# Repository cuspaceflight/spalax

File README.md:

# Spalax

This repository contains the schematics, PCB designs and firmware for a 10DOF IMU system.

## Components

- [Firmware](firmware) - Firmware for the various IMU boards
- [GUI](gui) - A 3D visualisation GUI which renders in realtime data sent from an attached IMU board
- [Shared](shared) - A static library providing common functionality between the various software components
- [Util](util) - A collection of useful C++, python and bash utilities
- [PCB](pcb) - The KiCad PCB files for the Spalax IMU boards

## Build Requirements

- GCC v4.8+
- CMake v3.2+
- arm-none-eabi-gcc (firmware build)
- xorg-dev libgl1-mesa-dev libfreetype6-dev libglew-dev libglm-dev (GUI build)
- GLFW v3+ (GUI build) - see [glfw-install.sh](util/bash/glfw-install.sh)

## Compilation

Having installed all the dependencies simply run from the root directory of the repo

```bash
git submodule update --init --recursive
./util/bash/travis-build.sh
```

This will configure and compile all the different components. If you only wish to configure a subset, just run the relevant section of [travis-build.sh](util/bash/travis-build.sh).

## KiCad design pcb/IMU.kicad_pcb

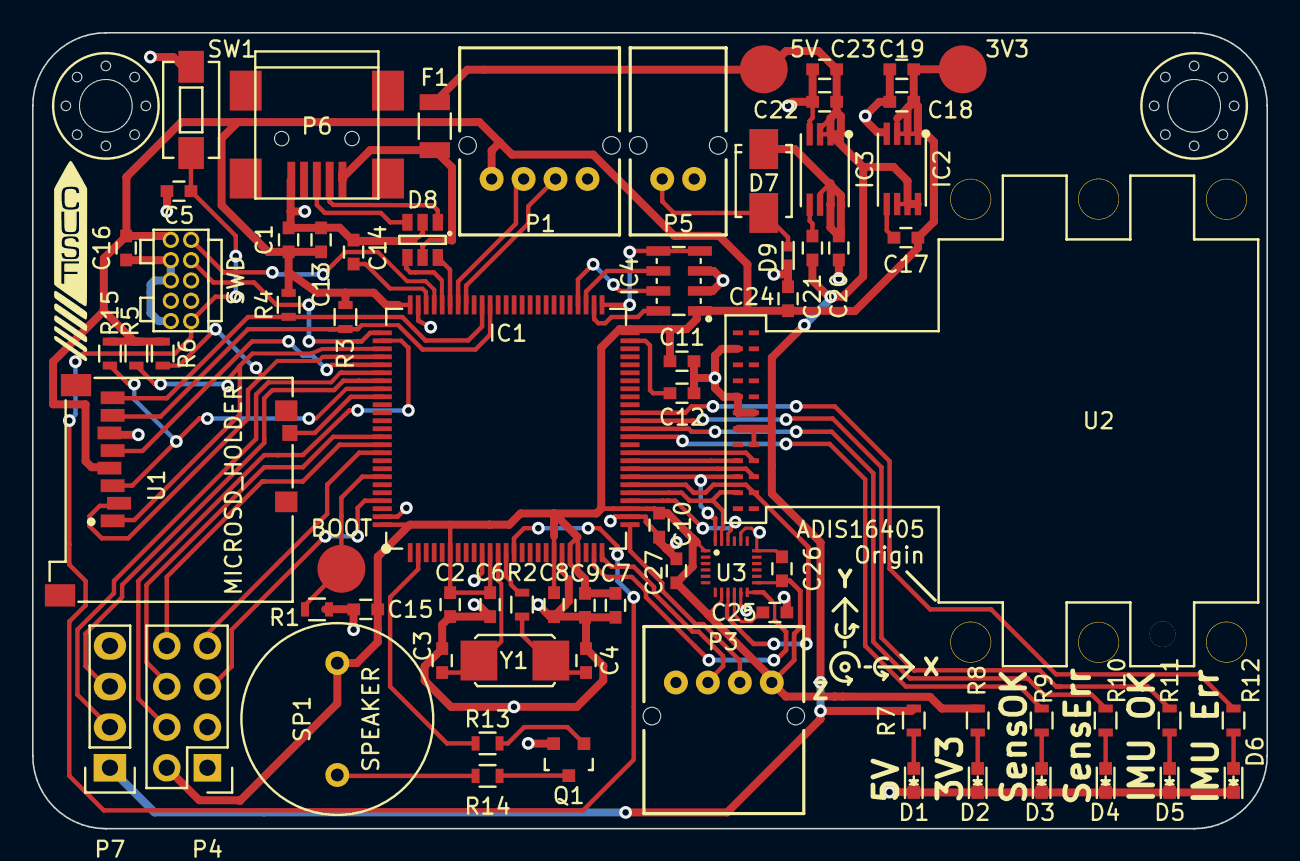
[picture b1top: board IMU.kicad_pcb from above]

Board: 2 copper layers, 77.2 x 49.8 mm, 75 parts (0 on the bottom side), 66 nets.

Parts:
3V3: 3V3; Measurement_Point_Round-SMD-Pad_Big
5V: 5V; Measurement_Point_Round-SMD-Pad_Big
BOOT: BOOT0; Measurement_Point_Round-SMD-Pad_Big
C1, C19, C23: 10µ; C_0603
C2, C5, C6, C8, C10, C11, C13, C15, C16, C24, C25, C27: 100n; C_0603
C3, C4: 15p; C_0603
C7, C18, C20, C22: 1µ; C_0603
C9, C26: 10n; C_0603
C12, C14: 2µ2; C_0603
C17, C21: 1n; C_0603
D1, D2, D3, D5: LED_GREEN; LED-0603
D4, D6: LED_RED; LED-0603
D7: S1A; SMA_Standard
D8: USBLC6-2; SOT-23-6
D9: CGA0402MLC-12G; R0402
F1: 500mA; MC33191
IC1: STM32F405VGT; LQFP100
IC2: ADP3335ARMZ-3.3; MSOP8
IC3: ADP3335ARMZ-5; MSOP8
IC4: MS5611-01BA03; MS5611-01BA
M3_MOUNT, M3_MOUNT#2: VAL**; M3_MOUNT
P1: UART1; S04B-PASK-2
P2: SWD; FTSH-105-01-F-D-K
P3: UART2; S04B-PASK-2
P4: SPI; Pin_Header_Straight_2x04
P5: BATTERY; S02B-PASK-2
P6: USB_OTG; USB_Mini-B
P7: CAN BUS; Pin_Header_Straight_1x04
Q1: Q_NMOS_GSD_PSV; SOT-23
R1: 10K; R_0603
R2, R13: 100; R_0603
R3, R4, R5, R6, R15: 47k; R_0603
R7: 1k; R_0603
R8, R9, R10, R11, R12: 510; R_0603
R14: 10; R_0603
SP1: SPEAKER; ABI-042-RC
SW1: SW_PUSH; SW_SPST_EVQPE1
U1: MICROSD_HOLDER; MEM2051
U2: ADIS16405BMLZ
U3: MOTION/POSITION-MPU-9250(QFN24); QFN24G-0.4-3X3MM
Y1: 8M; XTAL50x32

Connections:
+3V3: 3V3.1, C1.1, C2.1, C6.1, C7.1, C8.1, C9.1, C10.1, C11.1, C13.1, C15.1, C16.1, C17.1, C18.1, C19.1, C24.1, C26.2, C27.1, IC1.6, IC1.11, IC1.19, IC1.21, IC1.22, IC1.28, IC1.50, IC1.75, IC1.100, IC2.1, IC2.2, IC2.3, IC4.1, P1.1, P2.1, P3.1, P4.2, R3.1, R4.1, R5.1, R6.1, R8.2, R15.1, SP1.1, U1.4, U3.1, U3.8, U3.13
+5V: 5V.1, C21.1, C22.1, C23.1, F1.2, IC2.6, IC2.7, IC2.8, IC3.1, IC3.2, IC3.3, P7.1, R7.2, U2.10, U2.11, U2.12
+BATT: C20.1, D7.1, IC3.6, IC3.7, IC3.8
/Altimeter/ALT_CSB: IC1.51, IC4.4, IC4.5
/Altimeter/ALT_SCLK: IC1.52, IC4.8
/Altimeter/ALT_SDI: IC1.54, IC4.7
/Altimeter/ALT_SDO: IC1.53, IC4.6
/BOOT0: BOOT.1, IC1.94, R1.2
/CAN1_RX: IC1.81, P7.2
/CAN1_TX: IC1.82, P7.3
/DATA_RDY: IC1.97, P4.5
/IntertialSensors/ADIS_IRQ: IC1.34, U2.7
/IntertialSensors/MISO: IC1.31, U2.4, U3.9
/IntertialSensors/MOSI: IC1.32, U2.5, U3.24
/IntertialSensors/MPU_IRQ: IC1.24, U3.12
/IntertialSensors/SCLK: IC1.30, U2.3, U3.23
/IntertialSensors/~ADIS_RESET: IC1.35, U2.8
/IntertialSensors/~ADIS_SS: IC1.33, U2.6
/IntertialSensors/~MPU_SS: IC1.29, U3.22
/Power/USB5V: D8.5, F1.1, P6.1
/SDCard/CARD_DETECT: IC1.84, U1.9
/SDCard/SDIO_CK: IC1.80, U1.5
/SDCard/SDIO_CMD: IC1.83, R15.2, U1.3
/SDCard/SDIO_D0: IC1.65, R3.2, U1.7
/SDCard/SDIO_D1: IC1.66, R4.2, U1.8
/SDCard/SDIO_D2: IC1.78, R5.2, U1.1
/SDCard/SDIO_D3: IC1.79, R6.2, U1.2
/SPI3_MISO: IC1.90, P4.8
/SPI3_MOSI: IC1.91, P4.7
/SPI3_NSS: IC1.77, P4.4
/SPI3_SCK: IC1.89, P4.6
/SWDCLK: IC1.76, P2.4
/SWDIO: IC1.72, P2.2
/StatusIndicators/Buzzer: IC1.2, R13.2
/StatusIndicators/IMU: IC1.39, R11.2
/StatusIndicators/Sensors: IC1.37, R9.2
/StatusIndicators/~IMU: IC1.40, R12.2
/StatusIndicators/~Sensors: IC1.38, R10.2
/USART1_RX: IC1.69, P1.2
/USART1_TX: IC1.68, P1.3
/USART2_RX: IC1.26, P3.2
/USART2_TX: IC1.25, P3.3
/USB/OTG_DS_DP: D8.4, IC1.71
/USB/OTG_FS_DM: D8.6, IC1.70
/~RST: C5.1, IC1.14, P2.10, SW1.2
GND: C1.2, C2.2, C3.2, C4.2, C5.2, C6.2, C7.2, C8.2, C9.2, C10.2, C11.2, C12.2, C13.2, C14.2, C15.2, C16.2, C18.2, C19.2, C20.2, C22.2, C23.2, C24.2, C25.1, C26.1, C27.2, D1.1, D2.1, D3.1, D4.1, D5.1, D6.1, D8.2, D9.1, IC1.10, IC1.20, IC1.27, IC1.74, IC1.99, IC2.4, IC3.4, IC4.2, IC4.3, P1.4, P2.3, P2.5, P2.9, P3.4, P4.1, P4.3, P5.2, P6.5, P7.4, Q1.2, R1.1, SW1.1, U1.6, U2.13, U2.14, U2.15, U2.21, U3.11, U3.18, U3.20
unnamed: C3.1, IC1.12, Y1.1
unnamed: C4.1, R2.2, Y1.2
unnamed: C12.1, IC1.49
unnamed: C14.1, IC1.73
unnamed: C17.2, IC2.5
unnamed: C21.2, IC3.5
unnamed: C25.2, U3.10
unnamed: D1.2, R7.1
unnamed: D2.2, R8.1
unnamed: D3.2, R9.1
unnamed: D4.2, R10.1
unnamed: D5.2, R11.1
unnamed: D6.2, R12.1
unnamed: D7.2, D9.2, P5.1
unnamed: D8.1, P6.2
unnamed: D8.3, P6.3
unnamed: IC1.13, R2.1
unnamed: Q1.1, R13.1
unnamed: Q1.3, R14.1
unnamed: R14.2, SP1.2

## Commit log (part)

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2015-10-30 add ADIS16405BMLZ symbol and footprint
    Analog Devices kindly provide downloadable footprints and schematic symbols for
    the sensor. Unfortunately they're in a format which requires running a quite god
    awful tool to convert them into something usable. After firing up the Windows 10
    VM image I've got lying around, I finally got the damn things in KiCad format.
    Add them to the repo to save some other poor fool the effort.
    [1] http://www.analog.com/en/design-center/packaging-quality-symbols-footprints/symbols-and-footprints.html
2015-10-30 PCB/.gitignore: ignore KiCad backup files
2015-11-01 README: add link to some resources
2015-11-03 Added ADIS16405BMLZ schematic to InertialSensors sheet.
2015-11-03 Added Altimeter work by Alex Clowes
2015-11-04 remove special library
2015-11-04 PCB/IMU.sh: replace Earth symbols with Ground symbols
    Best be consistent!
2015-11-05 PCB/IMU.sch: add global labels for each pin assignment
2015-11-05 PCB: wire up altimeter to SPI2
2015-11-11 Basic firmware setup
2015-11-12 ekf-notes: fix type mathbf -> mathbb
2015-11-12 ekf-notes: move paragraph on setting predicted state components
    The paragraph on imposing certain predicted state components was in a
    non-logical place.
2015-11-12 ekf-notes: add some words on extending to linear motion
2015-11-12 ekf-notes: fix subscript of quaternion parameterisation
2015-11-12 README: add link to Madgwick's paper
2015-11-13 Revert to commit before last to fix bugs introduced by last commit
2015-11-15 wire IMU sensors to SPI1
2015-11-15 PCB: add test point to allow manual toggling of BOOT0
2015-11-15 PCB: annotate schematic and remove unused SDIO pins
2015-11-15 PCB: update TODO (remove done items)
2015-11-16 PCB: place components around STM32
    Those components whose placing is required to be close to particular pads have
    been placed and routed.
2015-11-16 PCB: swap some GPIO pin assignment to improve layout
    We have considerable freedom wrt GPIO pin locations. Route the inertial sensor's
    data ready line to a useful side of the chip.
2015-11-16 PCB: re-draw the ADIS16405 symbol to be less ugly
2015-11-16 PCB: fix footprint name of ADIS16450
2015-11-16 add ESD protection
2015-11-17 Updated README.md with information on how to configure Firmware and GUI builds.
2015-11-17 Further gitignore fixes.
2015-11-17 add simple Travis CI configuration
    Add .travis.yml and associated .editoconfig to support a minimal build of the
    firmware on Travis CI.
    The configuration selects Trusty as the build machine since it is the earliest
    version of Ubuntu LTS which includes the ARM GCC toolchain. (And the only one
    available on Travis.)
2015-11-18 PCB: SDCard: check Farnell numbers & footprints
2015-11-18 PCB: USB: check Farnell numbers & footprints
2015-11-18 PCB: re-import netlist with new footprints
2015-11-18 PCB: add xml2farnell.py script
    (Complete with unicode fixes)
2015-11-18 Add 2x4 pin header footprint for SPI connector
2015-11-18 PCB: add first pass at Farnell BOM
2015-11-29 Initial work on kalman filter - currently incomplete and in need of major cleanup
2015-11-30 Fixed Firmware build.
2015-12-02 update ADIS16405BMLZ footprint to have bigger pads
2015-12-04 Edit design rules so mimimums are (at least) m2fc values
2015-12-05 Move components to likely final locations and adjust some trace widths
2015-12-13 Move status LED outputs to pins 33 to 36 of the microcontroller
2015-12-14 Fixed bug where the indices of the jacobians were swapped, resulting in rather strange behaviour.
    The filter now works very well, the only problem remaining is roll isn't always resolved correctly. I'm not sure this is a deficiency of the filter, however, as the magnetometer on the board I am usi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
2015-12-19 Reduced number of long traces in ground plane by shuffling a number of components around. Also reduced the length of the PCB as an added bonus.
    The silkscreen is currently messed up as a result of these changes - I've not had time to fix it.
2016-01-11 Added an MPU-9250 on the same SPI bus as the ADIS sensor. The PCB routing is a first draft and I may tweak it a bit further.
    I had to change the track spacing tolerance from 0.2mm to 0.19mm to be able to wire up the sensor.
2016-01-20 Added badthinghandler written by James Timmins
2016-01-22 Added outline for mpu9250 driver
    Added ID check to ADIS16405 driver
    Minor tweaks to badthinghandler
2016-01-28 Changed SD Card resistors to 47K and changed ADIS reset to be attached to a GPIO pin instead.
2016-01-28 Add IMU axes and origin to PCB
2016-01-28 Imported new netlist into PCBNew and placed new footprints.
2016-01-28 Further PCB routing.
2016-01-29 Updated MPU9250 schematic part to match MPU-9250
    Fixed directionality of hierarchical pins
2016-01-31 Remove old Gerbers, add zip of gerbers sent to manufacturing.
2016-02-08 Pin and board configuration
2016-02-09 update pcb for paste generation
2016-03-12 MPU fixes
2016-03-12 firmware:mpu9520: explicitly ignore argument to thread
    ChibiOS threads may take an argument used to initialise them. The MPU9250 threa
    does not but we should explicitly indicate this both to the compiler *and* to
    humans.
2016-03-13 firmware:mpu9250: add gyro self-test to init sequence
    Re-jig mpu9250_init() to use a table of registers and values to make it a little
    easier to edit. Also call (and check return value of) mpu9250_self_test_gyro()
    to perform a self-test on the gyroscope.
    It's non-obvious where to find the application note referenced in the datasheet
    on self-testing. Instead I've cribbed from other MPU9250 drivers and implemented
    the same self-test algorithm.
2016-03-13 firmware:mpu9250: implement accelerometer self-test as well
2016-03-14 firmware:mpu9250: re-factor self-test
    The previous implementation ran the gyroscope self test at the same time as the
    accelerometer self test. This is a Bad Idea since they may interfere with each
    other. Re-factor the code to do them sequentially. Also remove the needlessly
    complex mean-taking code.
2016-03-14 firmware: enable USB and USB serial
    Add ChibiOS configuration to enable USB peripheral mode and USB serial console
    driver.
2016-03-14 firmware: add stub serial console
    Add a simple serial console implementation. This just uses the stock ChibiOS
    shell provider with no extra commands.
2016-03-15 firmware:mpu9250: add minimal AK8963 information
    On the MPU9250, the magnetometer is a separate AK8963 within the same package.
    From peering at example code (and datasheets) it appears that this is controlled
    at arm's length via the MPU9250's I2C slave support.
    Note: this means out current mpu9250_burst_read() implementation is wrong.
    Add a list of AK8963 registers and the I2C address of the AK8963 packaged within
    the MPU9250.
2016-03-20 Prevent main loop from terminating as for some reason it breaks USB when it does.
2016-03-21 Started work to make the messaging system generic as this should hopefully allow large amounts of the code base to be shared (e.g state estimation, communication interfaces, etc.)
    Updated Frontier.Engine
2016-03-21 Further formatting fixes.
2016-03-24 Fixed bug where message dispatch was using the number of initialized producers not consumers
2016-03-24 Added missing files
2016-03-25 Added Component State tracking System and added memory fences to the messaging system to ensure messages are never passed to a not fully initialized consumer.
2016-03-26 Fixed Firmware build
2016-03-27 Enabled verbose builds
2016-03-28 Updated build instructions
2016-03-28 Updated Frontier.Engine
2016-03-31 GUI now renders data.
    Removed incorrect magno reading code from mpu9250. I think you have to use the MPU9250's external I2c bus to talk to the magnetometer, although the datasheet is not particularly enlightening in this 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
2016-06-03 Working MPU9250 magnetometer, started working on trying to communicate with the ADIS sensor.
2016-06-03 MPU9250 magnetometer fully configured and automatically being read by the built in I2C Master at 100Hz.
2016-06-04 Changed messaging producer to take the packet size. This makes it clearer how many packets can be in flight at once and also potentially allows the usage of faster memory pools
2016-06-16 ADIS mostly working
2016-06-23 Changed to using cusf-messaging submodule
2016-07-31 Added MinGW Support
    Avionics.GUI can now be compiled using MinGW
2016-08-02 Updated submodules
2016-08-05 Changed magno update to just use heading, however, it doesn't work correctly and I'm not sure if this is because of flawed logic or an error in implementation - so I have left it disabled.
2016-08-06 Travis CI build will now also compile the Avionics GUI
2016-08-07 The heading-based magnetometer orientation estimation now correctly handles the discontinuity around heading 0 and seems to be working correctly now.
2016-08-12 Further work getting magnetometer to work correctly
2016-08-18 Repo re-arrangement
2016-08-19 Fix USB driver.
2016-08-19 Folder rename
2016-08-20 Moved IMU specific files from cusf-messaging
2016-08-20 Created template can_telemetry component.
2016-08-25 Added ADIS to StateDetailView
2016-08-26 Added CAN support to m3imu
2016-08-26 MPU9250 and ADIS16405 can share the SPI bus
2016-08-26 More extensible multipacket can support
2016-08-27 Per board configuration
2016-08-27 Fixed initialization order
2016-08-27 Added explicit rate limiting
2016-10-24 GUI Compilation
    Added a toolchain for compiling the GUI
2016-10-28 Updated gitignore
2016-10-31 Finished off Extractor
2016-11-02 Fixed build
2016-11-03 Cleanup and enabled warnings
2016-11-04 Added QUEST algorithm.
    Not fully tested yet, but appears to be working.
2016-11-08 Removed TestQuest::TestDisturbed as I think the logic behind it was flawed
2016-11-09 Fixed overzealous gitignore
2016-11-22 Started work migrating USB and CAN telemetry systems to CUSF Messaging
2016-11-22 Extractor will now throw an error if no valid connection found
2016-11-23 CMake tweaks
2016-11-25 Worked around GCC 4.8 standard library bug (missing ifstream move assignment).
2016-11-25 Minor tweaks to build system
2016-11-28 Added additional calibration techniques, including an ellipsoid fit which yields very good results
2016-12-18 Added papers list
2017-01-05 Updated to latest version of CUSF Messaging
2017-01-06 Fixed m3imu firmware build
2017-01-07 Moved Extractor to CUSF Messaging
2017-01-20 Added GPS and MS5611 Altitude Comparison Tool
2017-01-25 New calibration/sensor configuration system
2017-01-27 Fixed Altitude build and added plot markers to GPS map plotter
2017-01-28 Cleanup unused files
2017-01-29 State Estimation using Quest Algorithm, needs optimisation but suitable as a proof of concept
    Made X axis the principal "forward" axis instead of Y.
    Added Davenport Q Method
    Altered TestQuest to only check that the solution minimises the loss function, not that it produces the
    original quaternion (as this isn't necessarily guaranteed).
2017-01-29 Added ability to not link with FATFS
2017-02-04 The state of every component is now sent every 5 seconds.
    Disabled compilation of state estimators for m3imu
2017-02-14 Fixed incorrect state estimate rate reporting
2017-02-14 Disabled MPU9250 low pass filtering
2017-02-15 Configured GUI to run state estimator - currently broken
2017-02-16 Kalman filter can now be compiled with either 32-bit or 64-bit precision
2017-02-22 Further testing of kalman filter
2017-03-09 Further work trying to isolate kalman filter's gyroscope problems
2017-03-20 Minor optimisations to kalman filter and fixes to undefined behaviour in tests.
2017-03-20 Further work on position support
2017-03-22 Multiple tweaks to get kalman filter working
2017-03-28 Further work on kalman filter
    Current issue is axis misalignment between magnetometer and accelerometer
2017-03-30 Further tooling for analysis
2017-03-31 Data Extractor now only stores requested data
2017-04-07 Tweaks to Kalman Filter and graph plotting and data extraction utilities
2017-04-10 Removed unnecessary kalman states - fixes to wmm_util
2017-04-24 Misc ADIS work
2017-04-26 Further work on ADIS
2017-04-28 Fixes to tests
2017-05-05 Further work on plotting utilities
2017-05-12 Fixed Compilation
2017-08-16 cusf-messaging version bump

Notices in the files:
parts and their libraries:
Copyright 2015 Accelerated Designs. All rights reserved.
